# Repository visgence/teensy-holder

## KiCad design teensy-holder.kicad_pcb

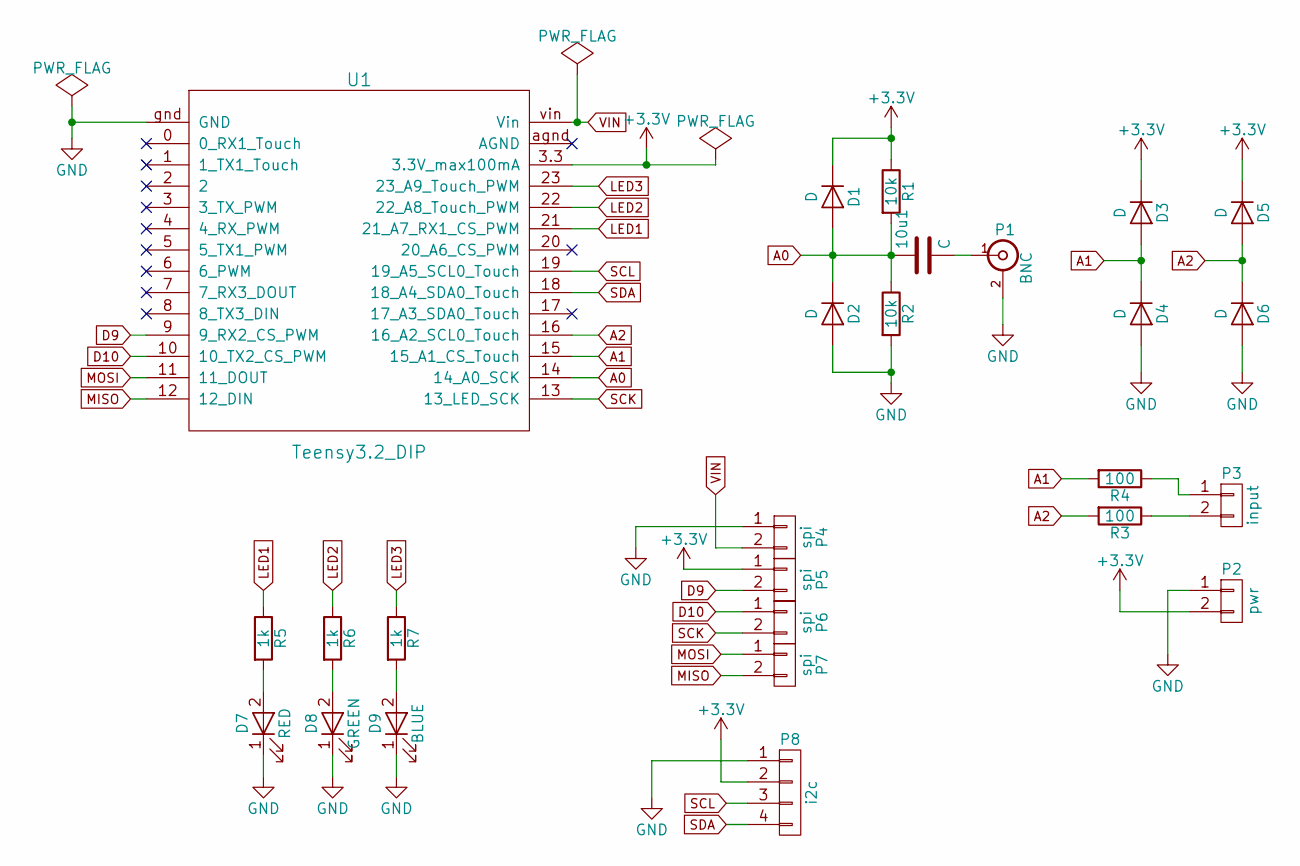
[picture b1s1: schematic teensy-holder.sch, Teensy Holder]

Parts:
10u1: C; SM1206_VIS
D1, D2, D3, D4, D5, D6: D; D_SOD-323
D7: RED; LED_0603
D8: GREEN; LED_0603
D9: BLUE; LED_0603
P1: BNC; BNC_TE
P2: pwr; Term3.5-2
P3: input; Term3.5-2
P4, P5, P6, P7: spi; Term3.5-2
P8: i2c; Pin_Header_Straight_1x04_Pitch2.54mm
R1, R2: 10k; SM0603_VIS
R3, R4: 100; SM0603_VIS
R5, R6, R7: 1k; SM0603_VIS
U1: Teensy3.2_DIP; Teensy31_DIP

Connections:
+3V3: D1.1 (K), D3.1 (K), D5.1 (K), P2.2, P5.1, P8.2, R1.1, U1.3.3 (3.3V_max100mA)
A0: 10u1.1, D1.2 (A), D2.1 (K), R1.2, R2.1, U1.14 (14_A0_SCK); also elsewhere on the board
A1: D3.2 (A), D4.1 (K), R4.2, U1.15 (15_A1_CS_Touch)
A2: D5.2 (A), D6.1 (K), R3.2, U1.16 (16_A2_SCL0_Touch)
D9: P5.2, U1.9 (9_RX2_CS_PWM)
D10: P6.1, U1.10 (10_TX2_CS_PWM)
GND: D2.2 (A), D4.2 (A), D6.2 (A), D7.1 (K), D8.1 (K), D9.1 (K), P1.2 (Ext), P2.1, P4.1, P8.1, R2.2, U1.gnd (GND)
LED1: R5.1, U1.21 (21_A7_RX1_CS_PWM)
LED2: R6.1, U1.22 (22_A8_Touch_PWM)
LED3: R7.1, U1.23 (23_A9_Touch_PWM)
MISO: P7.2, U1.12 (12_DIN)
MOSI: P7.1, U1.11 (11_DOUT)
unnamed 12: 10u1.2, P1.1 (In); also elsewhere on the board
unnamed: D7.2 (A), R5.2
unnamed: D8.2 (A), R6.2
unnamed: D9.2 (A), R7.2
unnamed: P3.1, R4.1
unnamed: P3.2, R3.1
SCK: P6.2, U1.13 (13_LED_SCK)
SCL: P8.3, U1.19 (19_A5_SCL0_Touch)
SDA: P8.4, U1.18 (18_A4_SDA0_Touch)
VIN: P4.2, U1.vin (Vin)

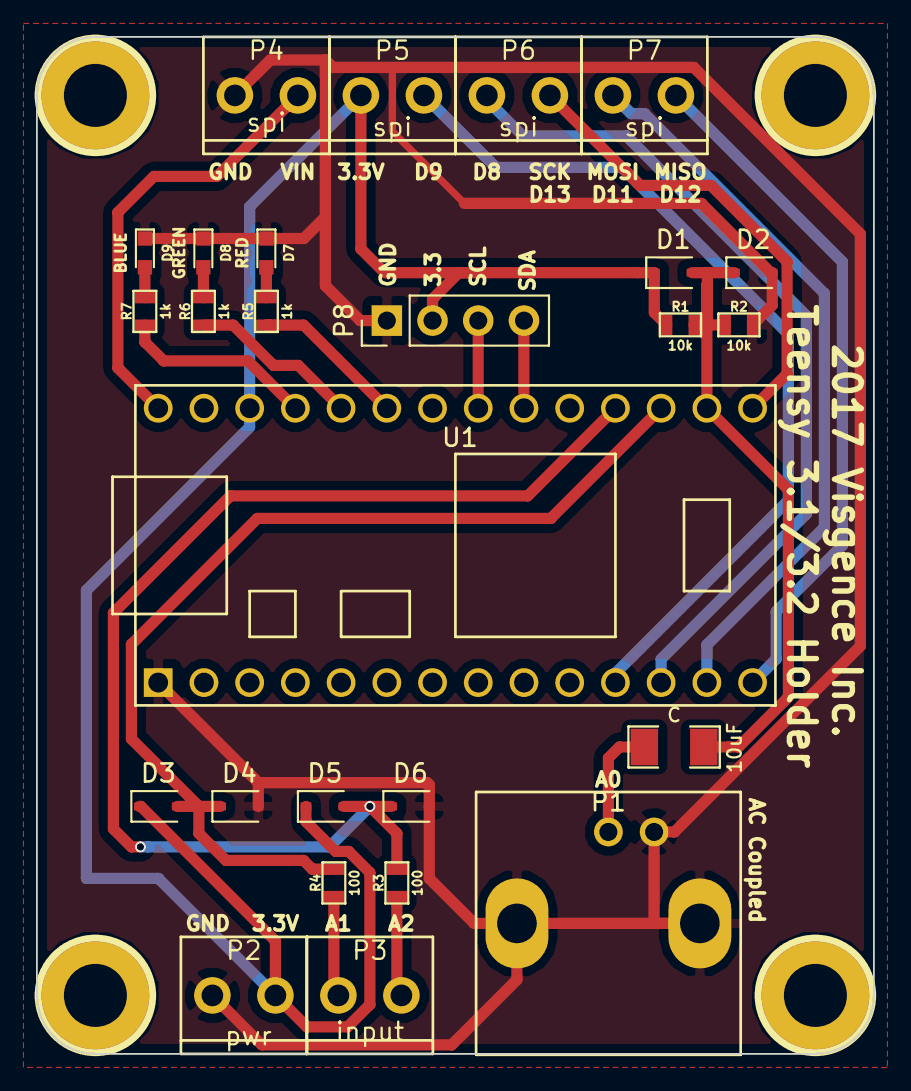
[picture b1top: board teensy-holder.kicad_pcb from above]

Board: 2 copper layers, 46.5 x 56.5 mm, 30 parts (0 on the bottom side), 22 nets.

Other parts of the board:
10uF: C; SM1206_VIS
h?: pin; 1pin_C
h?#2, h?#3, h?#4: pin; 1pin_C

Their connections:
A0: 10uF.1; also elsewhere on the board
unnamed 12: 10uF.2; also elsewhere on the board

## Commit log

2017-01-23 Added more parts, started board layout
2017-01-23 board layout
2017-01-23 Added 3.3v to term at bottom
2017-01-23 Added more ports, did some layout, swaped diodes
2017-01-23 Worked on routing
2017-01-25 Added Lables and logo
2017-01-25 Ran gerber tool
